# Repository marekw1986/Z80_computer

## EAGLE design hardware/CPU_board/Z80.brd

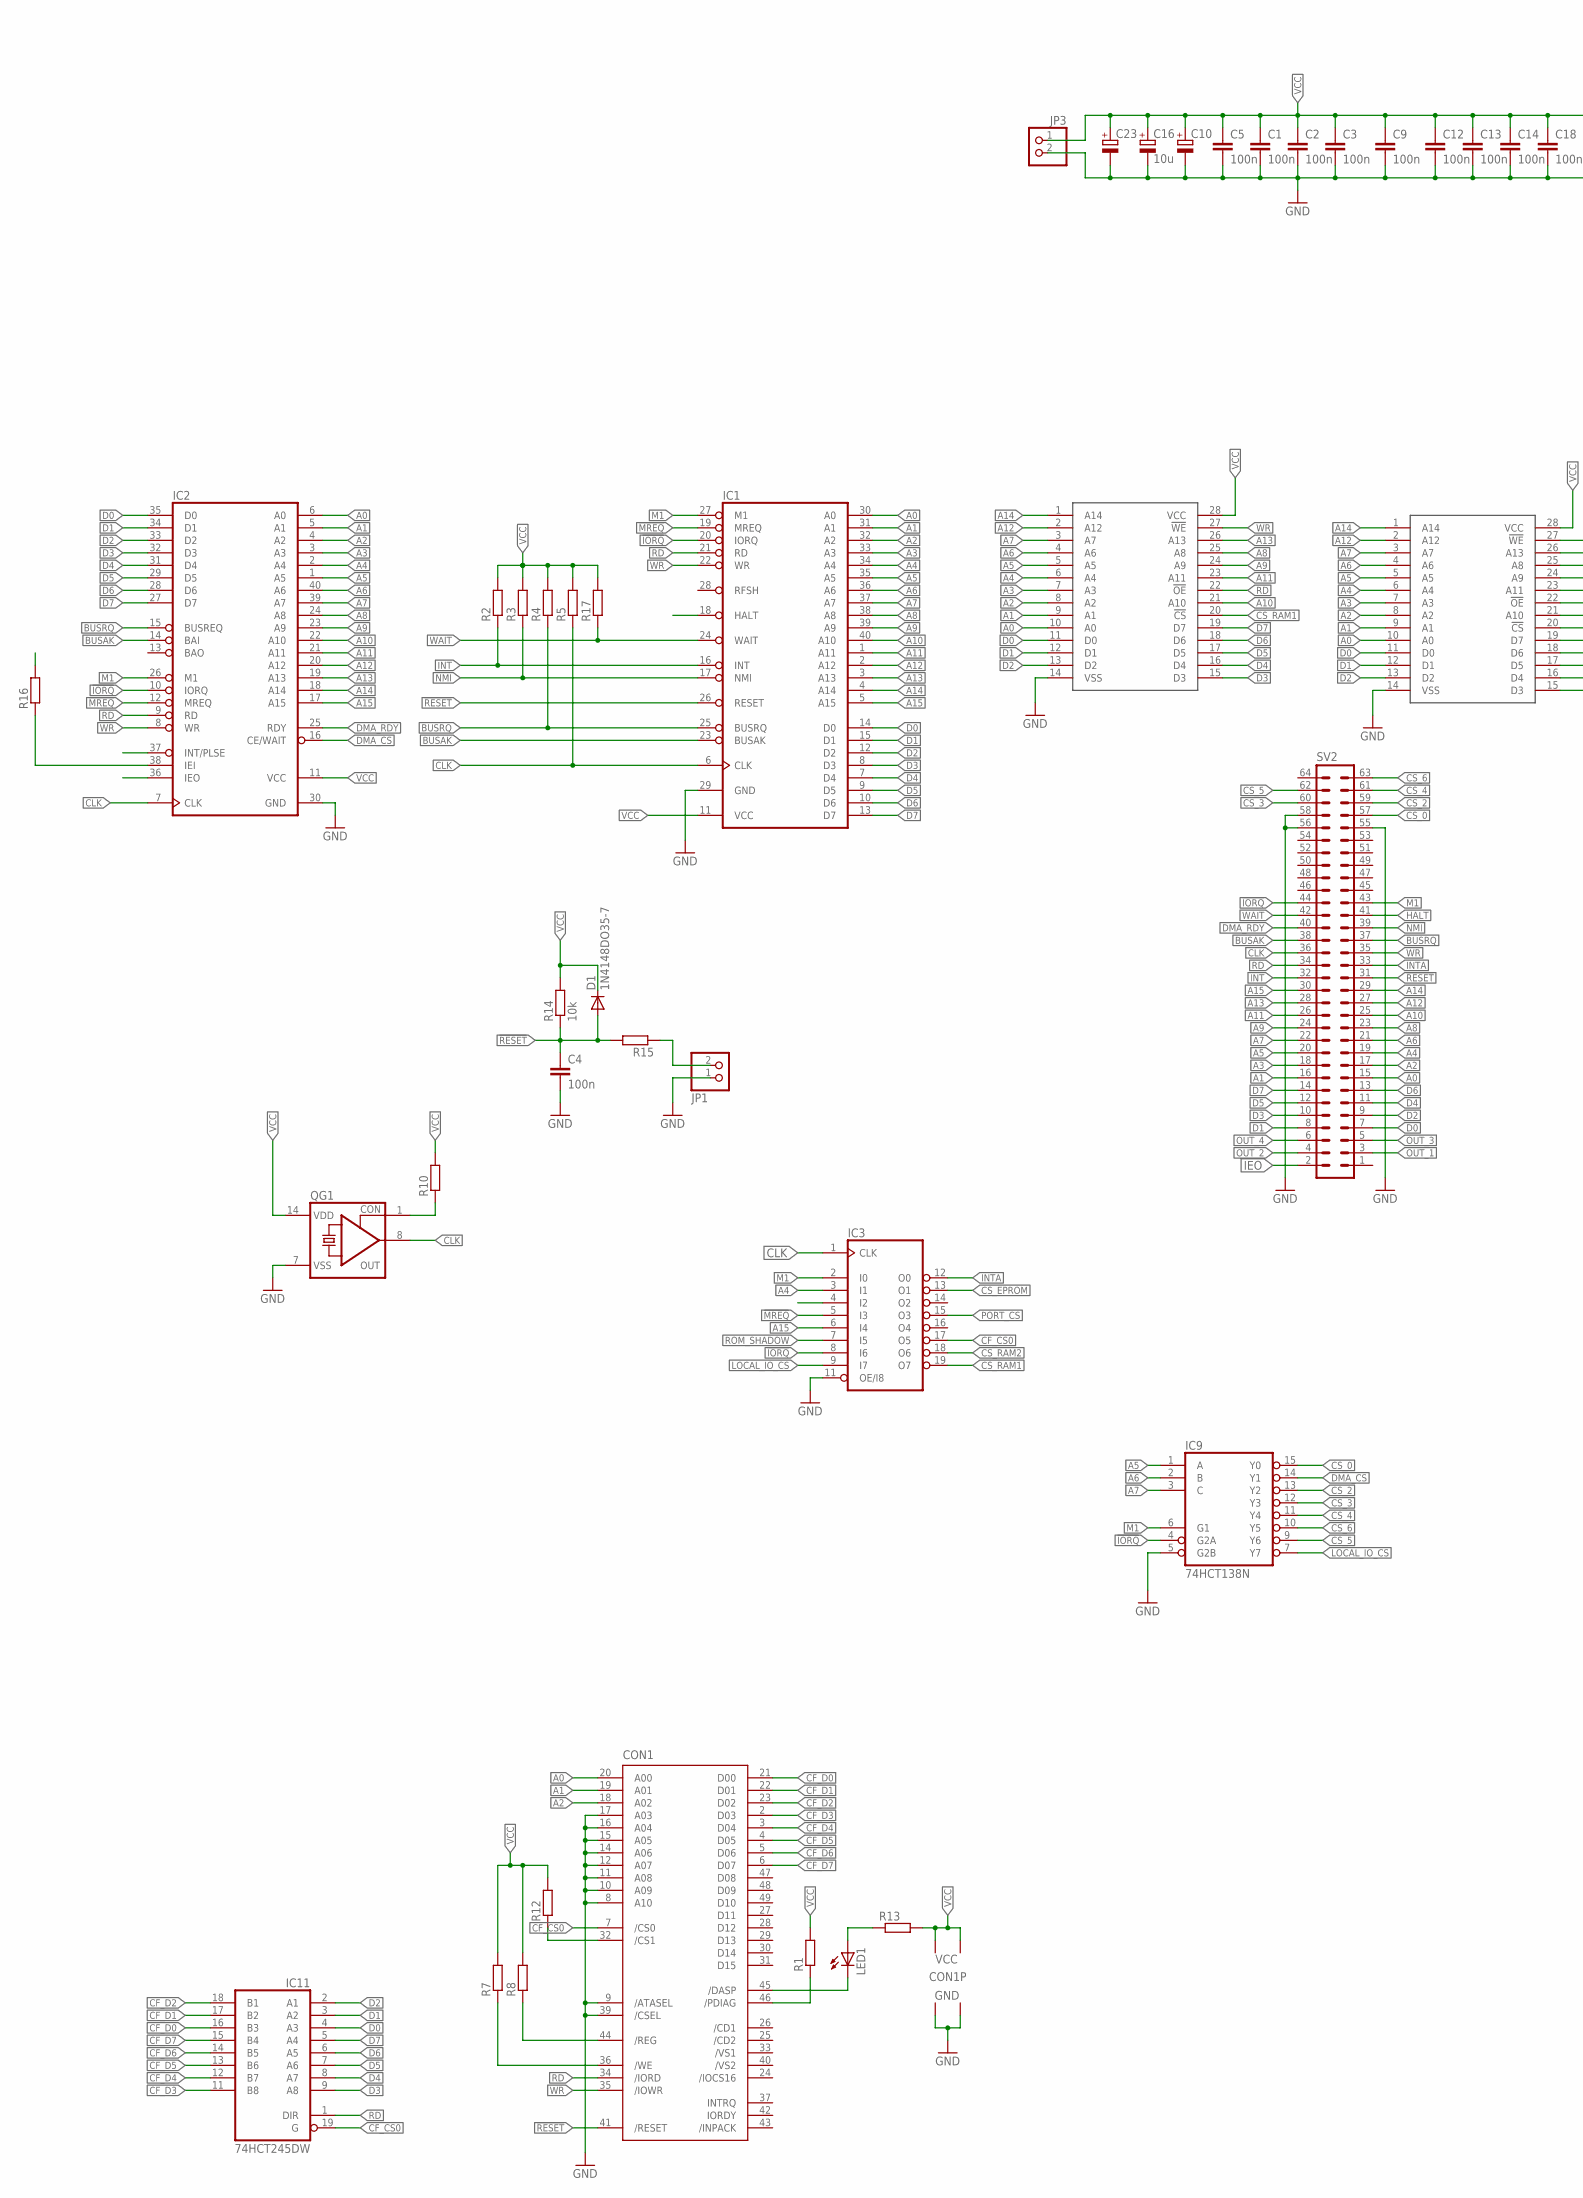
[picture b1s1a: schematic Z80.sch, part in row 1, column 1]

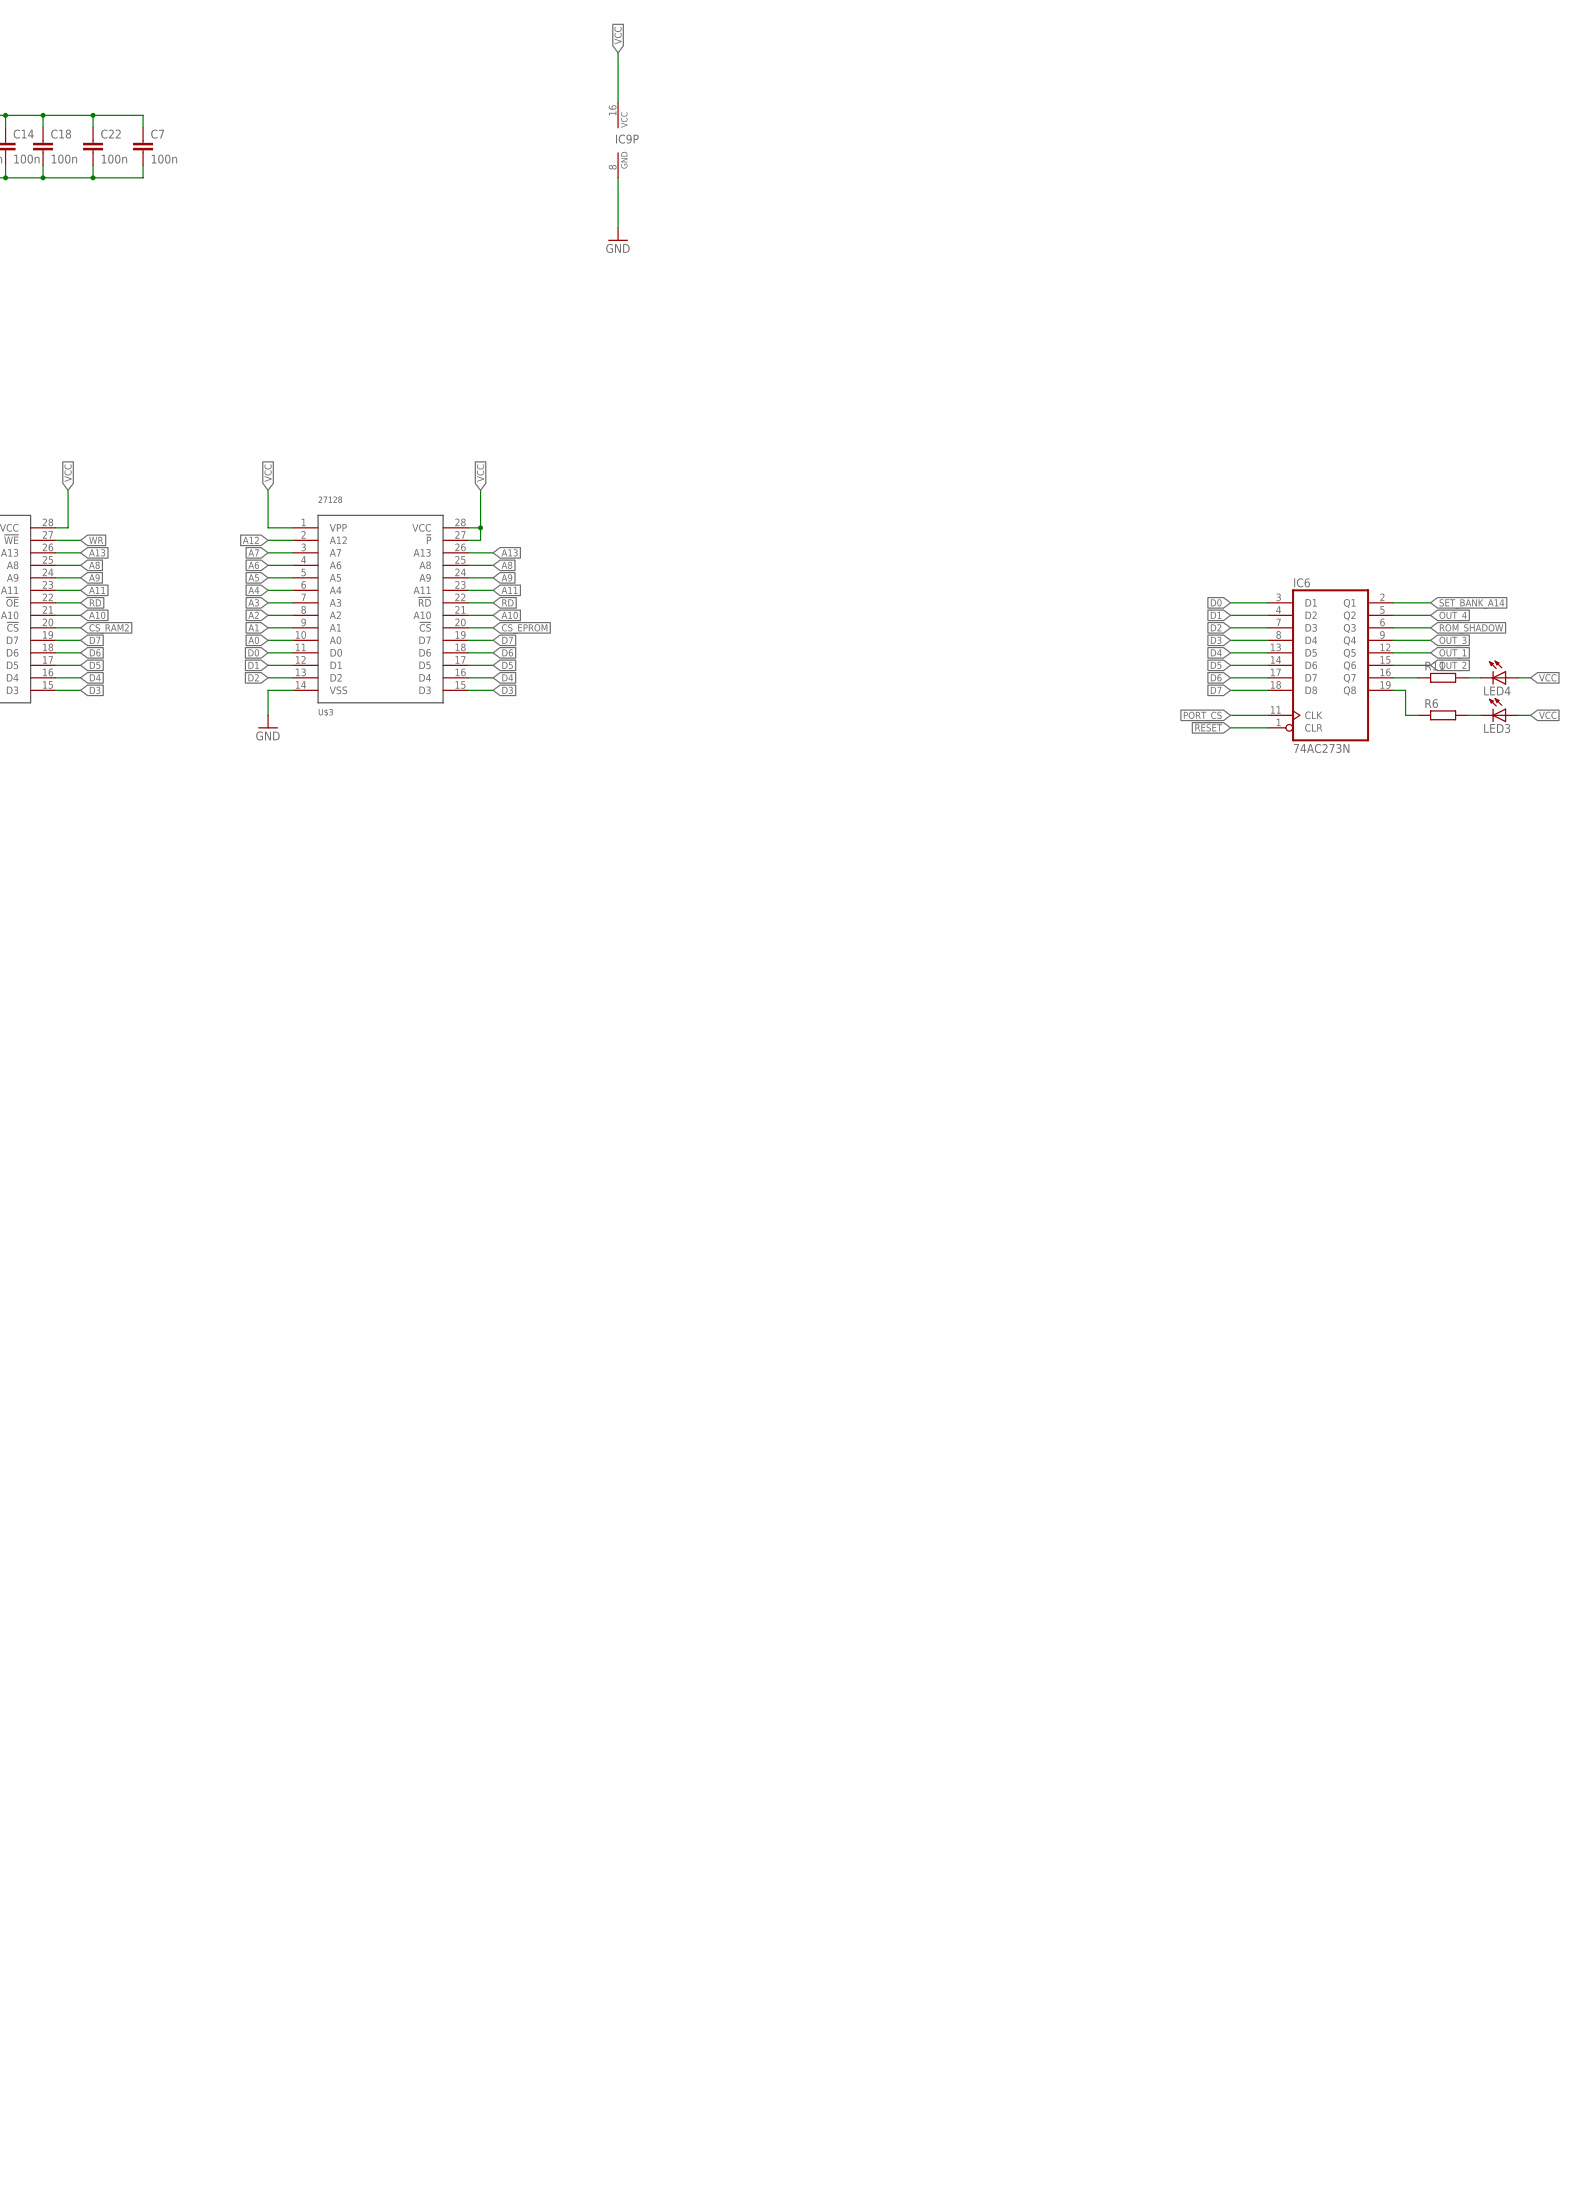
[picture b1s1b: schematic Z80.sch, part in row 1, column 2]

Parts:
C1, C2, C3, C9, C14: 100n; C1206
C4, C7, C18, C22: 100n; C0603
C5: 100n; C050-024X044
C10, C23: CPOL-EUE5-10.5; E5-10,5
C12, C13: 100n; C0805
C16: 10u; SMC_B
CON1: CF-CARD-IDE_MODE; MI20-50PD-SF
D1: 1N4148DO35-7; DO35-7
IC1: Z80CPU; DIL40
IC2: Z80DMA; DIL40
IC3: 16V8; DIL20
IC6: 74AC273N; DIL20
IC9: 74HCT138N; DIL16
IC11: 74HCT245DW; SO20W
JP1, JP3: PINHD-1X2; 1X02
LED1, LED3, LED4: LED5MM
QG1: CRYSTAL_RES-SG51; SG51
R1, R8: R-EU_0204/7; 0204/7
R2, R3, R6, R11: R-EU_R1206; R1206
R4, R5, R10, R13, R15, R17: R-EU_R0603; R0603
R7, R12: R-EU_0207/10; 0207/10
R14: 10k; 0204/7
R16: R-EU_0204/5; 0204/5
SV2: ML64L
U$2, U$4: 62256; DIL28-6
U$3: 27128; DIL28

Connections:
!IORQ: IC1.20 (IORQ), IC2.10 (IORQ), IC3.8 (I6), IC9.4 (G2A), SV2.44
!MREQ: IC1.19 (MREQ), IC2.12 (MREQ), IC3.5 (I3)
!RESET: C4.1, CON1.41 (/RESET), D1.A, IC1.26 (RESET), IC6.1 (CLR), R14.1, R15.2, SV2.31
A0: CON1.20 (A00), IC1.30 (A0), IC2.6 (A0), SV2.15, U$2.10 (A0), U$3.10 (A0), U$4.10 (A0)
A1: CON1.19 (A01), IC1.31 (A1), IC2.5 (A1), SV2.16, U$2.9 (A1), U$3.9 (A1), U$4.9 (A1)
A2: CON1.18 (A02), IC1.32 (A2), IC2.4 (A2), SV2.17, U$2.8 (A2), U$3.8 (A2), U$4.8 (A2)
A3: IC1.33 (A3), IC2.3 (A3), SV2.18, U$2.7 (A3), U$3.7 (A3), U$4.7 (A3)
A4: IC1.34 (A4), IC2.2 (A4), IC3.3 (I1), SV2.19, U$2.6 (A4), U$3.6 (A4), U$4.6 (A4)
A5: IC1.35 (A5), IC2.1 (A5), IC9.1 (A), SV2.20, U$2.5 (A5), U$3.5 (A5), U$4.5 (A5)
A6: IC1.36 (A6), IC2.40 (A6), IC9.2 (B), SV2.21, U$2.4 (A6), U$3.4 (A6), U$4.4 (A6)
A7: IC1.37 (A7), IC2.39 (A7), IC9.3 (C), SV2.22, U$2.3 (A7), U$3.3 (A7), U$4.3 (A7)
A8: IC1.38 (A8), IC2.24 (A8), SV2.23, U$2.25 (A8), U$3.25 (A8), U$4.25 (A8)
A9: IC1.39 (A9), IC2.23 (A9), SV2.24, U$2.24 (A9), U$3.24 (A9), U$4.24 (A9)
A10: IC1.40 (A10), IC2.22 (A10), SV2.25, U$2.21 (A10), U$3.21 (A10), U$4.21 (A10)
A11: IC1.1 (A11), IC2.21 (A11), SV2.26, U$2.23 (A11), U$3.23 (A11), U$4.23 (A11)
A12: IC1.2 (A12), IC2.20 (A12), SV2.27, U$2.2 (A12), U$3.2 (A12), U$4.2 (A12)
A13: IC1.3 (A13), IC2.19 (A13), SV2.28, U$2.26 (A13), U$3.26 (A13), U$4.26 (A13)
A14: IC1.4 (A14), IC2.18 (A14), SV2.29, U$2.1 (A14), U$4.1 (A14)
A15: IC1.5 (A15), IC2.17 (A15), IC3.6 (I4), SV2.30
BUSAK: IC1.23 (BUSAK), IC2.14 (BAI), SV2.38
BUSRQ: IC1.25 (BUSRQ), IC2.15 (BUSREQ), R4.1, SV2.37
CF_CS0: CON1.7 (/CS0), IC3.17 (O5), IC11.19 (G)
CF_D0: CON1.21 (D00), IC11.16 (B3)
CF_D1: CON1.22 (D01), IC11.17 (B2)
CF_D2: CON1.23 (D02), IC11.18 (B1)
CF_D3: CON1.2 (D03), IC11.11 (B8)
CF_D4: CON1.3 (D04), IC11.12 (B7)
CF_D5: CON1.4 (D05), IC11.13 (B6)
CF_D6: CON1.5 (D06), IC11.14 (B5)
CF_D7: CON1.6 (D07), IC11.15 (B4)
CLK: IC1.6 (CLK), IC2.7 (CLK), IC3.1 (CLK), QG1.8 (OUT), R5.1, SV2.36
CS_0: IC9.15 (Y0), SV2.57
CS_2: IC9.13 (Y2), SV2.59
CS_3: IC9.12 (Y3), SV2.60
CS_4: IC9.11 (Y4), SV2.61
CS_5: IC9.9 (Y6), SV2.62
CS_6: IC9.10 (Y5), SV2.63
CS_EPROM: IC3.13 (O1), U$3.20 (!CS)
CS_RAM1: IC3.19 (O7), U$4.20 (!CS)
CS_RAM2: IC3.18 (O6), U$2.20 (!CS)
D0: IC1.14 (D0), IC2.35 (D0), IC6.3 (D1), IC11.4 (A3), SV2.7, U$2.11 (D0), U$3.11 (D0), U$4.11 (D0)
D1: IC1.15 (D1), IC2.34 (D1), IC6.4 (D2), IC11.3 (A2), SV2.8, U$2.12 (D1), U$3.12 (D1), U$4.12 (D1)
D2: IC1.12 (D2), IC2.33 (D2), IC6.7 (D3), IC11.2 (A1), SV2.9, U$2.13 (D2), U$3.13 (D2), U$4.13 (D2)
D3: IC1.8 (D3), IC2.32 (D3), IC6.8 (D4), IC11.9 (A8), SV2.10, U$2.15 (D3), U$3.15 (D3), U$4.15 (D3)
D4: IC1.7 (D4), IC2.31 (D4), IC6.13 (D5), IC11.8 (A7), SV2.11, U$2.16 (D4), U$3.16 (D4), U$4.16 (D4)
D5: IC1.9 (D5), IC2.29 (D5), IC6.14 (D6), IC11.7 (A6), SV2.12, U$2.17 (D5), U$3.17 (D5), U$4.17 (D5)
D6: IC1.10 (D6), IC2.28 (D6), IC6.17 (D7), IC11.6 (A5), SV2.13, U$2.18 (D6), U$3.18 (D6), U$4.18 (D6)
D7: IC1.13 (D7), IC2.27 (D7), IC6.18 (D8), IC11.5 (A4), SV2.14, U$2.19 (D7), U$3.19 (D7), U$4.19 (D7)
DMA_CS: IC2.16 (CE/WAIT), IC9.14 (Y1)
DMA_RDY: IC2.25 (RDY), SV2.40
GND: C1.2, C2.2, C3.2, C4.2, C5.2, C7.2, C9.2, C10.-, C12.2, C13.2, C14.2, C16.-, C18.2, C22.2, C23.-, CON1.1 (GND1), CON1.8 (A10), CON1.9 (/ATASEL), CON1.10 (A09), CON1.11 (A08), CON1.12 (A07), CON1.14 (A06), CON1.15 (A05), CON1.16 (A04), CON1.17 (A03), CON1.39 (/CSEL), CON1.50 (GND2), IC1.29 (GND), IC2.30 (GND), IC3.10 (GND), IC3.11 (OE/I8), IC6.10 (GND), IC9.5 (G2B), IC9.8 (GND), IC11.10 (GND), JP1.1, JP3.2, QG1.7 (VSS), SV2.55, SV2.56, SV2.58, U$2.14 (VSS), U$3.14 (VSS), U$4.14 (VSS)
HALT: IC1.18 (HALT), SV2.41
IEO: IC2.36 (IEO), SV2.2
INT: IC1.16 (INT), IC2.37 (INT/PLSE), R2.1, SV2.32
INTA: IC3.12 (O0), SV2.33
LOCAL_IO_CS: IC3.9 (I7), IC9.7 (Y7)
M1: IC1.27 (M1), IC2.26 (M1), IC3.2 (I0), IC9.6 (G1), SV2.43
unnamed: QG1.1 (CON), R10.1
unnamed: JP1.2, R15.1
unnamed: IC2.38 (IEI), R16.1
unnamed: IC6.16 (Q7), R11.1
unnamed: LED3.K (C), R6.2
unnamed: LED4.K (C), R11.2
unnamed: IC6.19 (Q8), R6.1
unnamed: CON1.44 (/REG), R8.1
unnamed: CON1.36 (/WE), R7.1
unnamed: CON1.46 (/PDIAG), R1.1
unnamed: LED1.A, R13.1
unnamed: CON1.45 (/DASP), LED1.K (C)
unnamed: CON1.32 (/CS1), R12.1
NMI: IC1.17 (NMI), R3.1, SV2.39
OUT_1: IC6.12 (Q5), SV2.3
OUT_2: IC6.15 (Q6), SV2.4
OUT_3: IC6.9 (Q4), SV2.5
OUT_4: IC6.5 (Q2), SV2.6
PORT_CS: IC3.15 (O3), IC6.11 (CLK)
RD: CON1.34 (/IORD), IC1.21 (RD), IC2.9 (RD), IC11.1 (DIR), SV2.34, U$2.22 (!OE), U$3.22 (!RD), U$4.22 (!OE)
ROM_SHADOW: IC3.7 (I5), IC6.6 (Q3)
SET_BANK_A14: IC6.2 (Q1)
VCC: C1.1, C2.1, C3.1, C5.1, C7.1, C9.1, C10.+, C12.1, C13.1, C14.1, C16.+, C18.1, C22.1, C23.+, CON1.13 (VCC2), CON1.38 (VCC1), D1.C, IC1.11 (VCC), IC2.11 (VCC), IC3.20 (VCC), IC6.20 (VCC), IC9.16 (VCC), IC11.20 (VCC), JP3.1, LED3.A, LED4.A, QG1.14 (VDD), R1.2, R2.2, R3.2, R4.2, R5.2, R7.2, R8.2, R10.2, R12.2, R13.2, R14.2, R16.2, R17.2, U$2.28 (VCC), U$3.1 (VPP), U$3.27 (!P), U$3.28 (VCC), U$4.28 (VCC)
WAIT: IC1.24 (WAIT), R17.1, SV2.42
WR: CON1.35 (/IOWR), IC1.22 (WR), IC2.8 (WR), IC3.4 (I2), SV2.35, U$2.27 (!WE), U$4.27 (!WE)

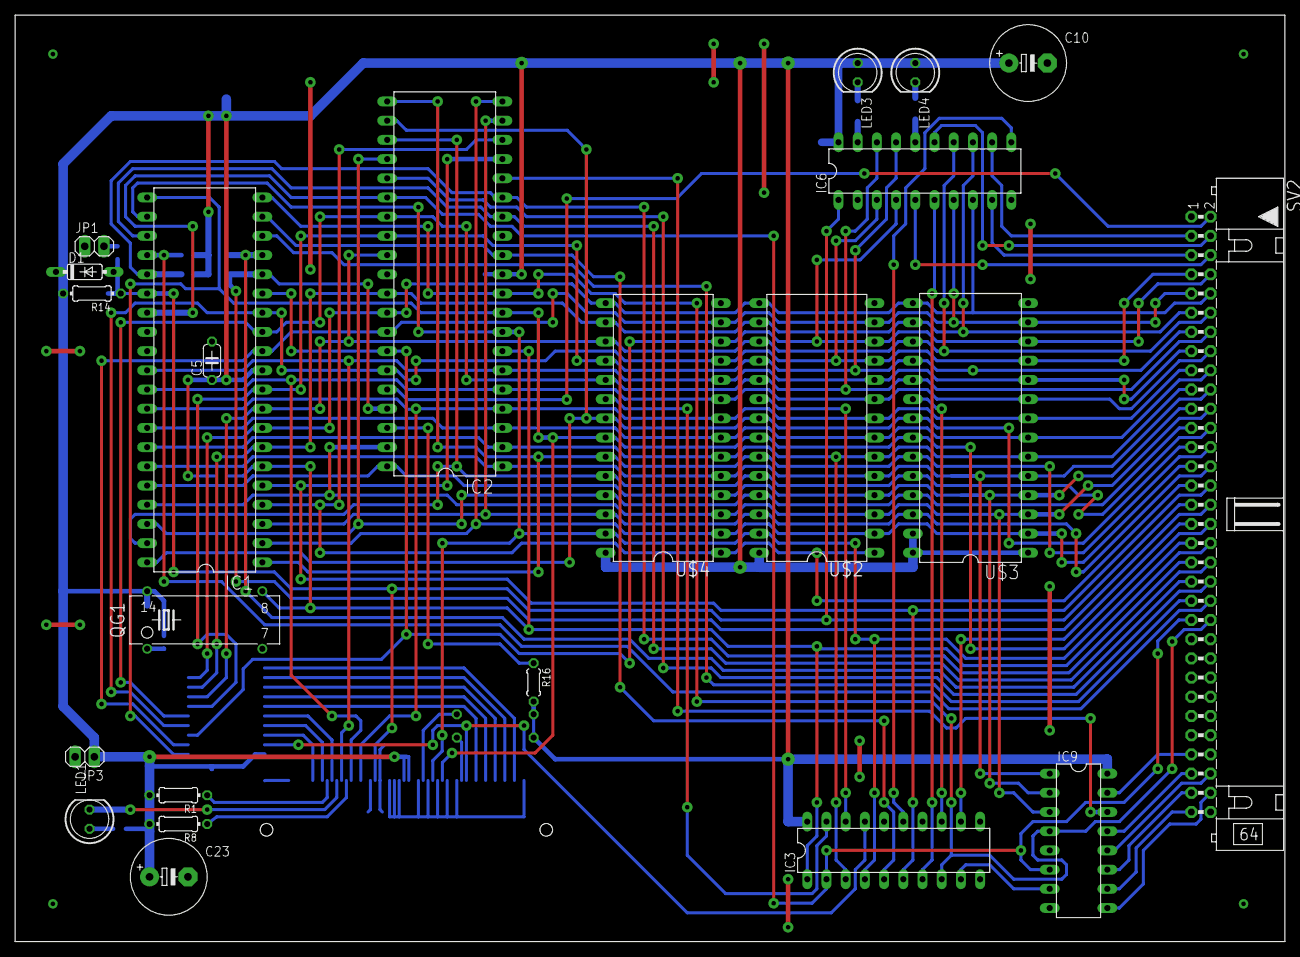
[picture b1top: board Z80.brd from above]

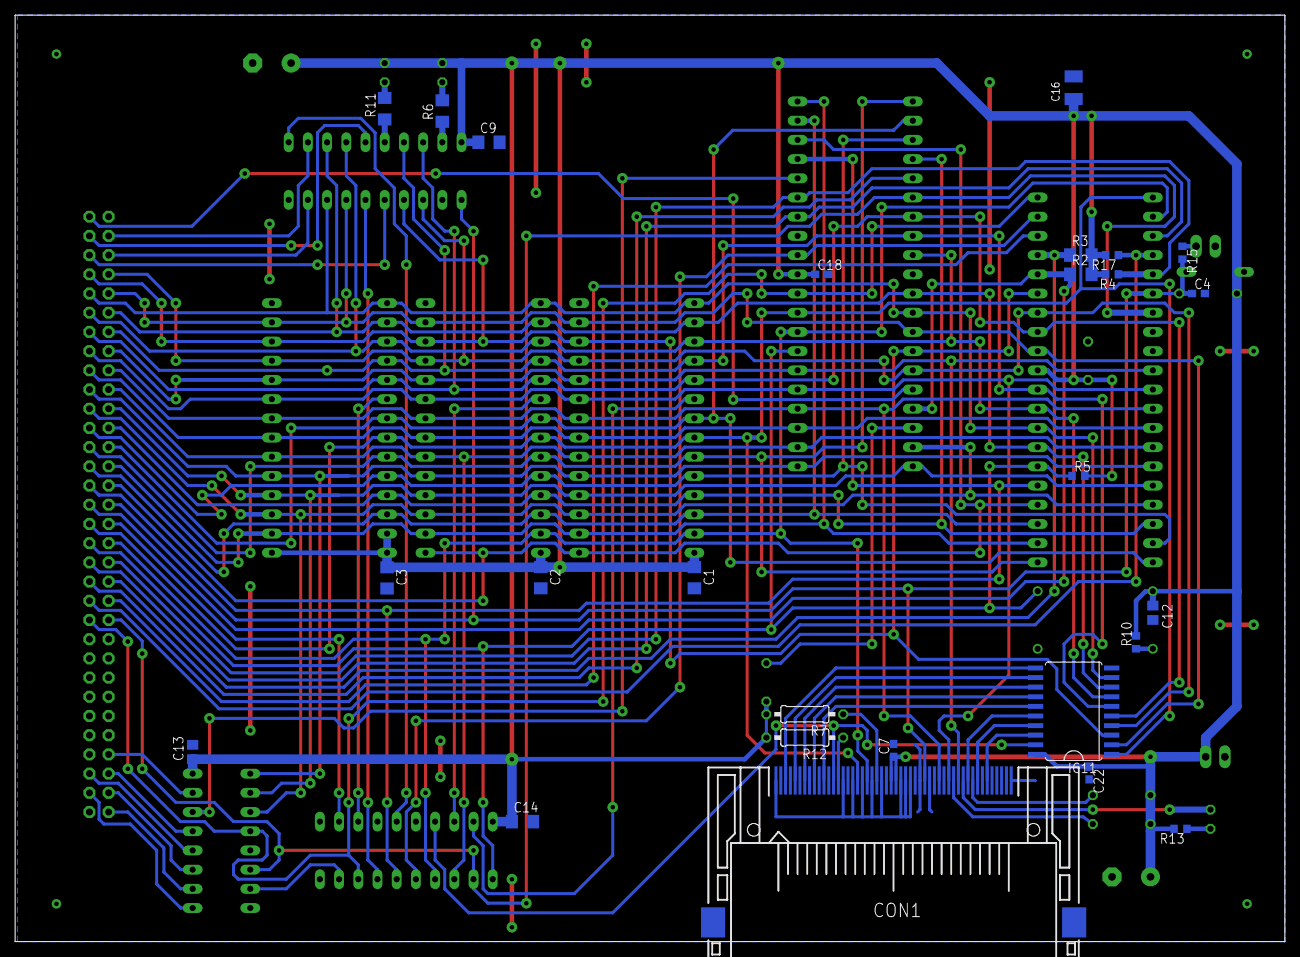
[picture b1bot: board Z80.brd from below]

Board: 2 copper layers, 167.9 x 122.5 mm, 49 parts (26 on the bottom side), 81 nets.

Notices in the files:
parts and their libraries:
SparkFun-Connectors: Licensing: Creative Commons ShareAlike 4.0 International - https://creativecommons.org/licenses/by-sa/4.0
